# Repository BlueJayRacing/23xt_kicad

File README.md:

# 23xt_kicad, JHU Blue Jay Racing Repository
This is the KiCad Repository for the JHU 23XT DAQ Sub-team.

## Installation and User Guide
GitHub & KiCad Guide: https://docs.google.com/document/d/1nFm-e38JEY4i58-0UFxqdLA5TKqWCrV3EDKR8jGpRfA/edit?usp=sharing 

As a summary, you should be using **KiCad Version 10.0**. All project will be modular, and you should be storing all your step files, symbols, & footprints within the created folders.

Schematic settings & layout settings are described in the guide, as well as component derating.

## Branch Guide
You should be working on a new branch for each revision of your board. It is only when your board gets ordered on JLC that it should be merged with the main branch.

<ins>Branch naming structure:</ins> [0X]-[boardname]_v[version]

Example:
> 01-main_board_v1

<ins>How-To Create a Branch:</ins>

```
git checkout -b [your_branch] main
git push -u origin [your_branch]
```

## KiCad Project Name

Create your KiCad project on YOUR branch, within your current project folder.

<ins>Project filepath:</ins> [your_folder]/[boardname]_v[X]

Example Path:
> 01-main_board/main_board_v1

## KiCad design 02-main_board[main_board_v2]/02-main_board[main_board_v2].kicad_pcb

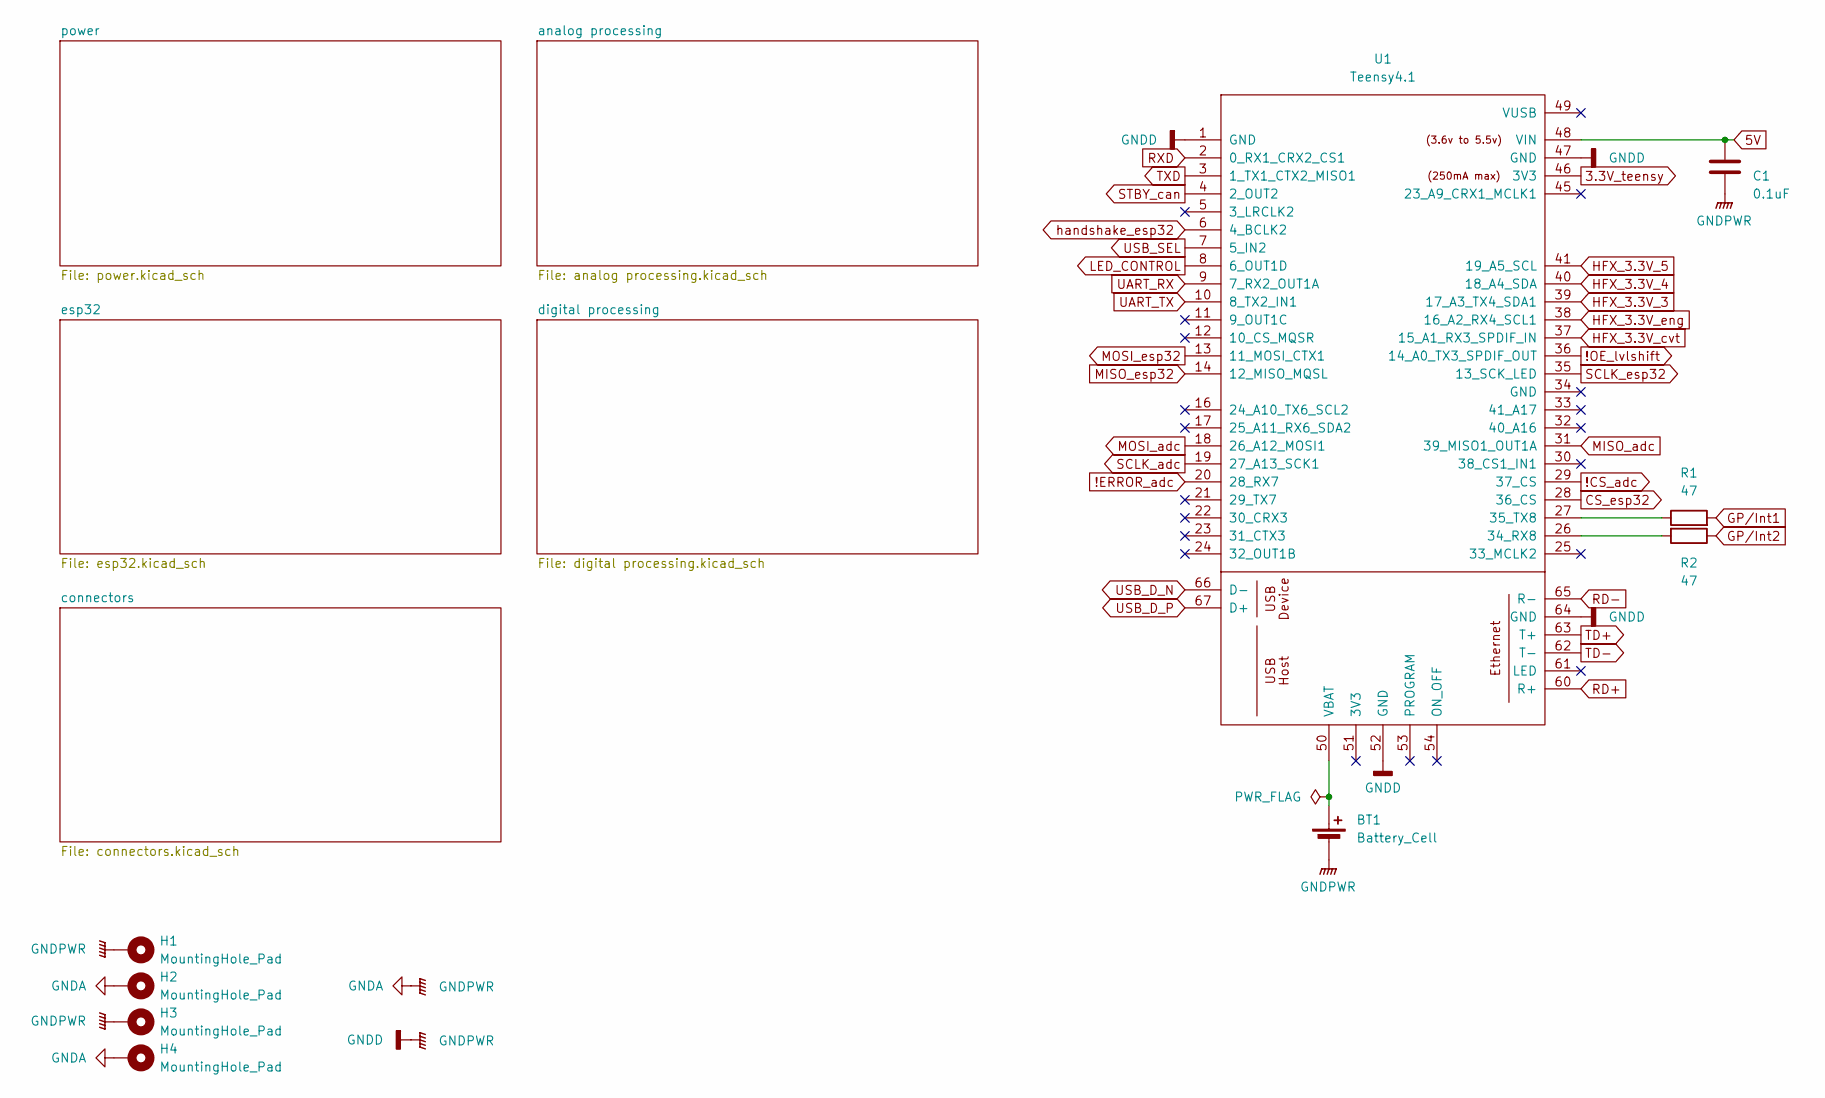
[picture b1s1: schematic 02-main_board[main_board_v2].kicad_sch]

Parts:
BT1: Battery_Cell; BatteryHolder_LINX_BAT-HLD-012-SMT
C1: 0.1uF; C_0603_1608Metric; MPN CC0603KRX7R9BB104; LCSC C14663
H1, H2, H3, H4: MountingHole_Pad; MountingHole_2.5mm_Pad
R1, R2: 47; R_0603_1608Metric; MPN RC0603JR-0747RL; LCSC C23182
U1: Teensy4.1; Teensy41_OG

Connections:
3.3V_teensy: U1.46 (3V3); also elsewhere on the board
5V: C1.2, U1.48 (VIN); also elsewhere on the board
!CS_adc: U1.29 (37_CS); also elsewhere on the board
!ERROR_adc: U1.20 (28_RX7); also elsewhere on the board
!OE_lvlshift: U1.36 (14_A0_TX3_SPDIF_OUT); also elsewhere on the board
CS_esp32: U1.28 (36_CS); also elsewhere on the board
GNDA: BT1.2 (-), C1.1, H1.1 (1_1), H2.1 (1_1), H3.1 (1_1), H4.1 (1_1), U1.1 (GND), U1.47 (GND), U1.52 (GND), U1.64 (GND); also elsewhere on the board
GP/Int1: R1.2; also elsewhere on the board
GP/Int2: R2.1; also elsewhere on the board
HFX_3.3V_3: U1.39 (17_A3_TX4_SDA1); also elsewhere on the board
HFX_3.3V_4: U1.40 (18_A4_SDA); also elsewhere on the board
HFX_3.3V_5: U1.41 (19_A5_SCL); also elsewhere on the board
HFX_3.3V_cvt: U1.37 (15_A1_RX3_SPDIF_IN); also elsewhere on the board
HFX_3.3V_eng: U1.38 (16_A2_RX4_SCL1); also elsewhere on the board
LED_CONTROL: U1.8 (6_OUT1D); also elsewhere on the board
MISO_adc: U1.31 (39_MISO1_OUT1A); also elsewhere on the board
MISO_esp32: U1.14 (12_MISO_MQSL); also elsewhere on the board
MOSI_adc: U1.18 (26_A12_MOSI1); also elsewhere on the board
MOSI_esp32: U1.13 (11_MOSI_CTX1); also elsewhere on the board
unnamed: BT1.1 (+), U1.50 (VBAT)
unnamed: R2.2, U1.26 (34_RX8)
unnamed: R1.1, U1.27 (35_TX8)
RD+: U1.60 (R+); also elsewhere on the board
RD-: U1.65 (R-); also elsewhere on the board
RXD: U1.2 (0_RX1_CRX2_CS1); also elsewhere on the board
SCLK_adc: U1.19 (27_A13_SCK1); also elsewhere on the board
SCLK_esp32: U1.35 (13_SCK_LED); also elsewhere on the board
STBY_can: U1.4 (2_OUT2); also elsewhere on the board
TD+: U1.63 (T+); also elsewhere on the board
TD-: U1.62 (T-); also elsewhere on the board
TXD: U1.3 (1_TX1_CTX2_MISO1); also elsewhere on the board
UART_RX: U1.9 (7_RX2_OUT1A); also elsewhere on the board
UART_TX: U1.10 (8_TX2_IN1); also elsewhere on the board
USB_D_N: U1.66 (D-); also elsewhere on the board
USB_D_P: U1.67 (D+); also elsewhere on the board
USB_SEL: U1.7 (5_IN2); also elsewhere on the board
handshake_esp32: U1.6 (4_BCLK2); also elsewhere on the board

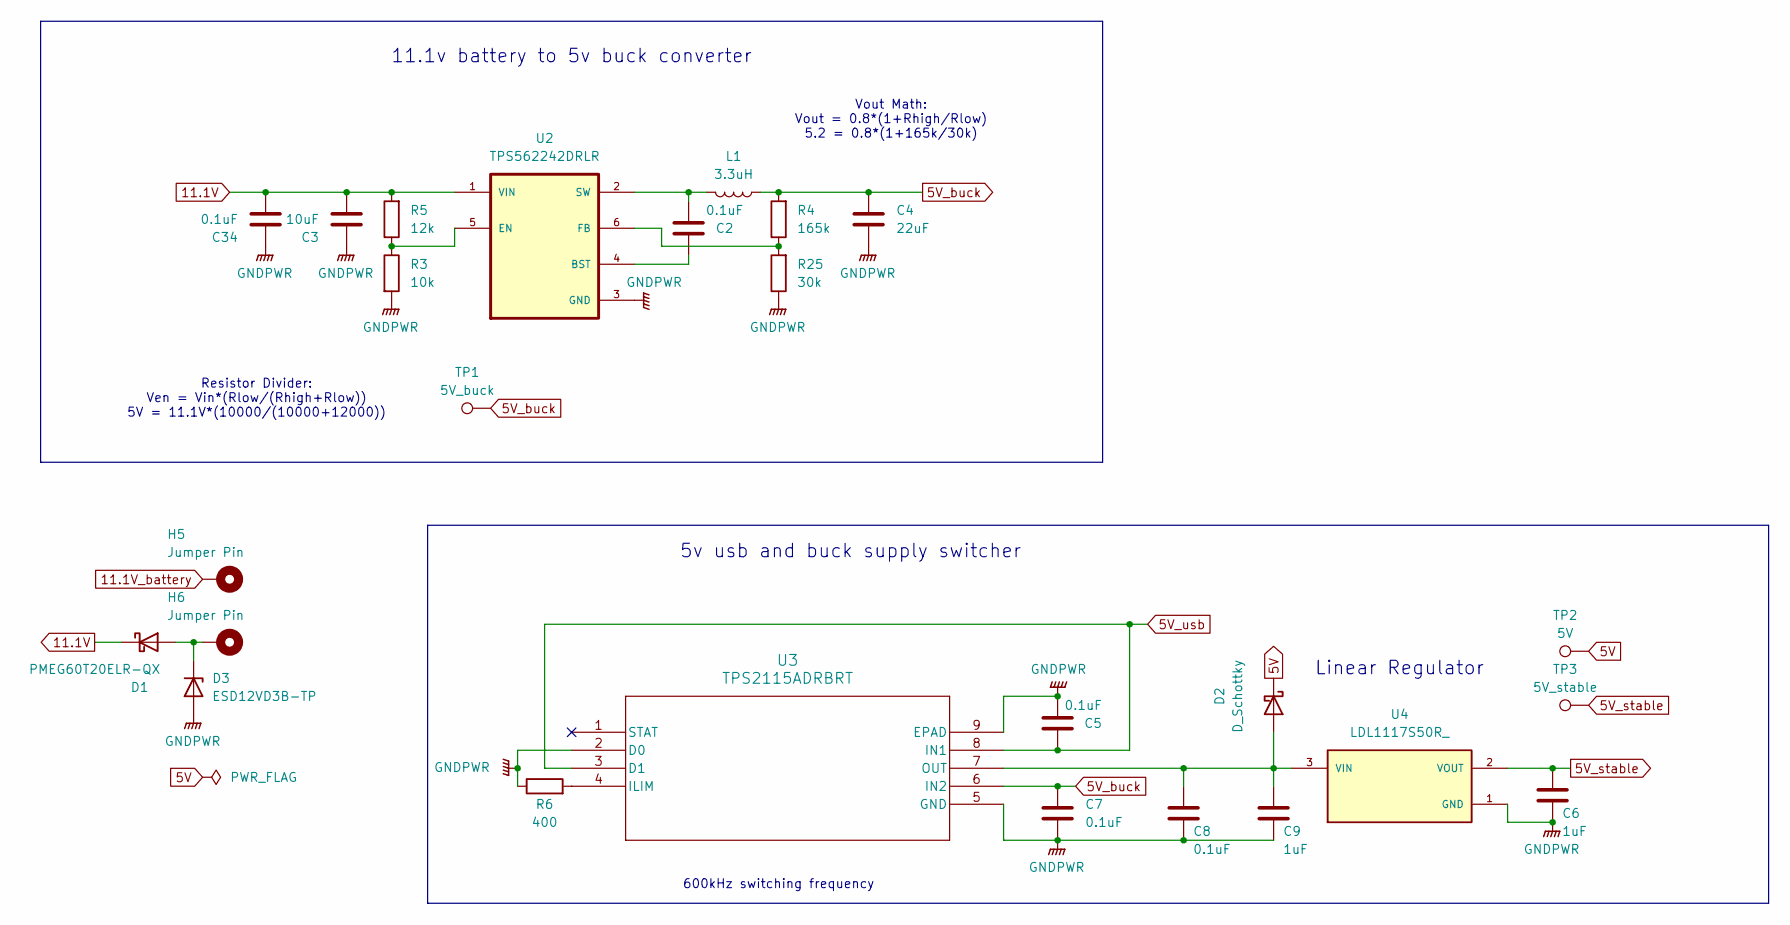
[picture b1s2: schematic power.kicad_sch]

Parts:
C2: 0.1uF; C_0603_1608Metric; MPN CL10B474KO8NNND; LCSC C14663
C3: 10uF; C_0603_1608Metric; MPN GMC10X5R106M16NT; LCSC C96446
C4: 22uF; C_0603_1608Metric; MPN GRM188R61A226ME15D; LCSC C59461
C5, C7, C8: 0.1uF; C_0603_1608Metric; MPN CC0603KRX7R9BB104; LCSC C14663
C6, C9: 1uF; C_0603_1608Metric; MPN CL10A105KA8NFNC; LCSC C15849
C34: 0.1uF; C_0603_1608Metric; MPN CL10A475KO8NNNC; LCSC C14663
D1: PMEG60T20ELR-QX; Nexperia_CFP3_SOD-123W
D2: D_Schottky; Nexperia_CFP3_SOD-123W
D3: ESD12VD3B-TP; D_SOD-323
H5, H6: Jumper Pin; PinHeader_1x01_P2.54mm_Vertical
L1: 3.3uH; IND_TAIYO_NRS4018_TAY; MPN NRS4018T3R3MDGJ
R3: 10k; R_0603_1608Metric; MPN CRCW060310K0FKEA; LCSC C25804
R4: 165k; R_0603_1608Metric; MPN RNCF0603DTE165K
R5: 12k; R_0603_1608Metric; MPN CRCW060312K0FKEA; LCSC C22790
R6: 400; R_0603_1608Metric; MPN RK73H1JTTD4020F
R25: 30k; R_0603_1608Metric; MPN TFAS0603R3002F-T5
TP1: 5V_buck; TestPoint_Pad_1.0x1.0mm
TP2: 5V; TestPoint_Pad_1.0x1.0mm
TP3: 5V_stable; TestPoint_Pad_1.0x1.0mm
U2: TPS562242DRLR; SOT50P160X60-6N; PARTREV A
U3: TPS2115ADRBRT; SON65P300X300X100-9N-D; MPN TPS2115ADRBR
U4: LDL1117S50R_; PARTREV 7

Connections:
5V: D2.1 (K), TP2.1 (1_1); also elsewhere on the board
5V_buck: C4.1, C7.1, L1.1, R4.2, TP1.1 (1_1), U3.6 (IN2)
5V_stable: C6.1, TP3.1 (1_1), U4.2 (VOUT), U4.4 (VOUT); also elsewhere on the board
5V_usb: C5.1, U3.3 (D1), U3.8 (IN1); also elsewhere on the board
11.1V: C3.2, C34.2, D1.1 (K), R5.2, U2.1 (VIN); also elsewhere on the board
11.1V_battery: H5.1 (1_1); also elsewhere on the board
GNDA: C3.1, C4.2, C5.2, C6.2, C7.2, C8.2, C9.2, C34.1, D3.2 (A), R3.2, R6.1, R25.1, U2.3 (GND), U3.2 (D0), U3.5 (GND), U3.9 (EPAD), U4.1 (GND); also elsewhere on the board
unnamed: D1.2 (A), D3.1 (K), H6.1 (1_1)
unnamed: C8.1, C9.1, D2.2 (A), U3.7 (OUT), U4.3 (VIN)
unnamed: C2.1, U2.4 (BST)
unnamed: R3.1, R5.1, U2.5 (EN)
unnamed: R4.1, R25.2, U2.6 (FB)
unnamed: C2.2, L1.2, U2.2 (SW)
unnamed: R6.2, U3.4 (ILIM)

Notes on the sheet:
Resistor Divider: Ven = Vin*(Rlow/(Rhigh+Rlow)) 5V = 11.1V*(10000/(10000+12000))
Vout Math: Vout = 0.8*(1+Rhigh/Rlow) 5.2 = 0.8*(1+165k/30k)
5v usb and buck supply switcher
Linear Regulator
600kHz switching frequency
11.1v battery to 5v buck converter

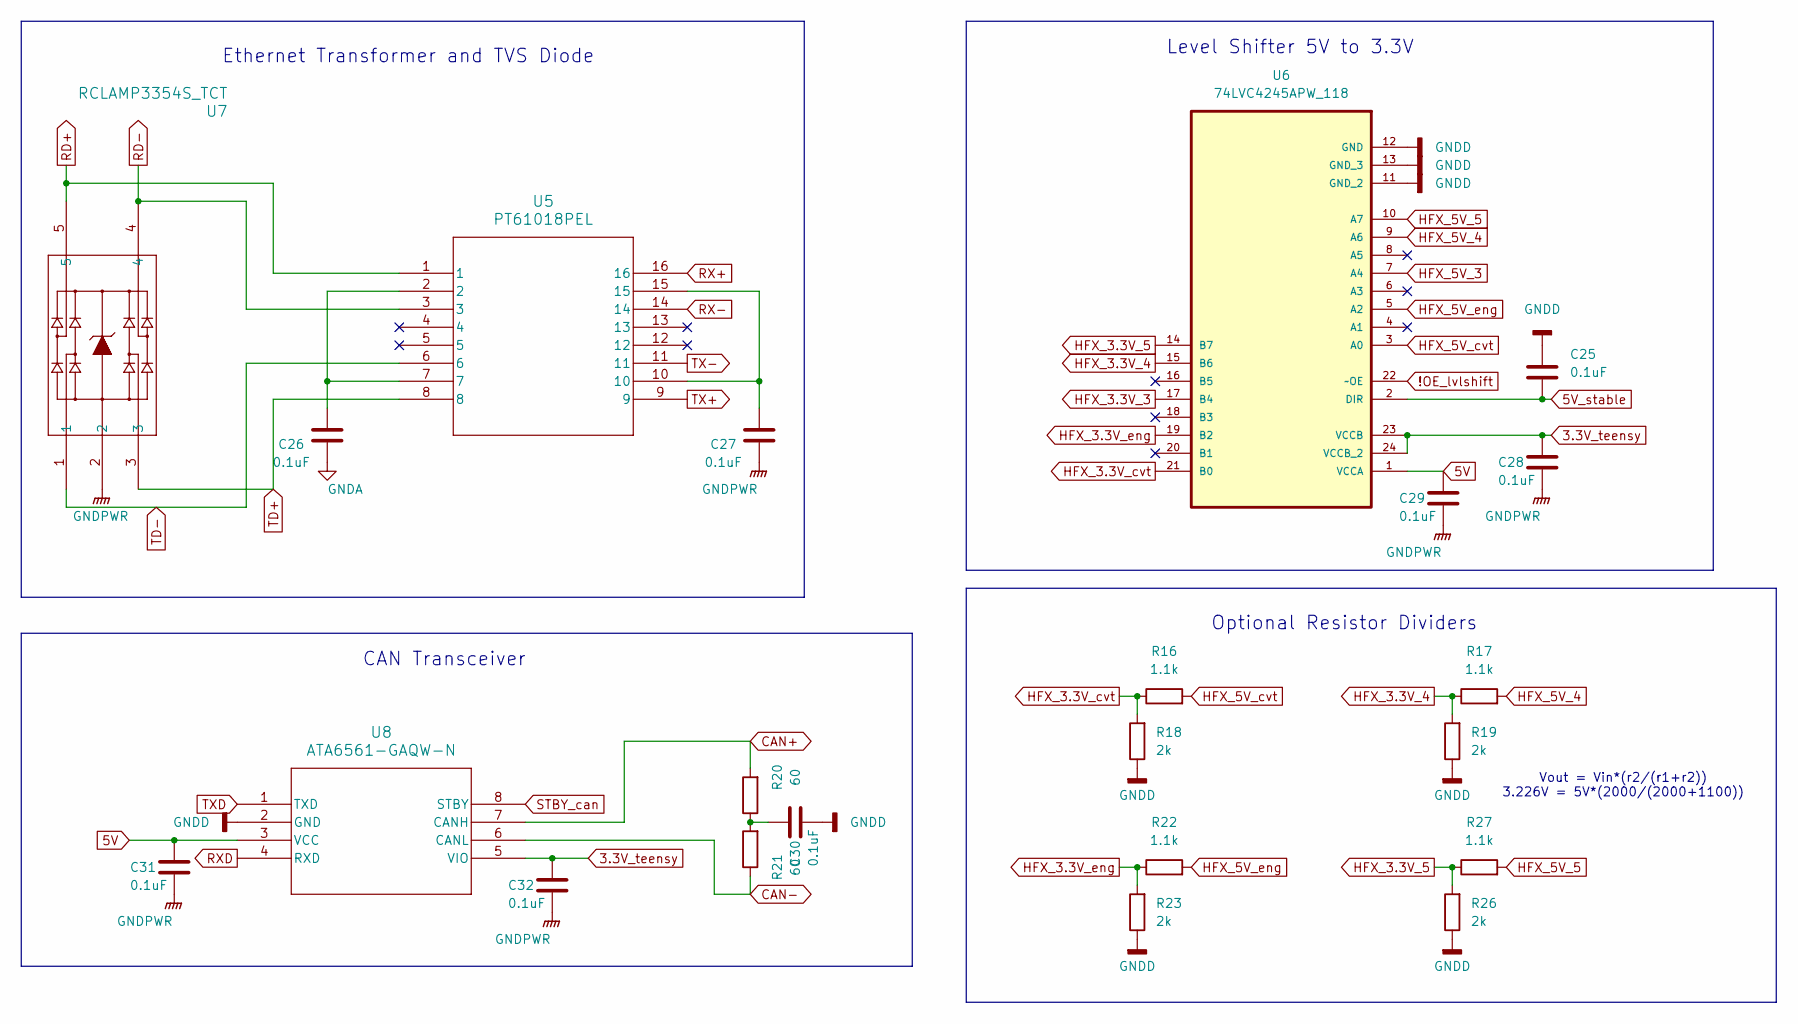
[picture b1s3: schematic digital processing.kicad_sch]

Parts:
C25, C26, C27, C28, C29, C30, C31, C32: 0.1uF; C_0603_1608Metric; MPN CC0603KRX7R9BB104; LCSC C14663
R16, R17, R22, R27: 1.1k; R_0603_1608Metric; MPN RT0603BRD071K1L
R18, R19, R23, R26: 2k; R_0603_1608Metric; MPN RC0603FR-072KL
R20, R21: 60; R_0603_1608Metric; MPN CRCW060360R4FKEA
U5: PT61018PEL; SOIC_PT61018PEL
U6: 74LVC4245APW_118
U7: RCLAMP3354S_TCT
U8: ATA6561-GAQW-N

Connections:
3.3V_teensy: C28.2, C32.2, U6.23 (VCCB), U6.24 (VCCB_2), U8.5 (VIO); also elsewhere on the board
5V: C29.2, C31.2, U6.1 (VCCA), U8.3 (VCC); also elsewhere on the board
5V_stable: C25.1, U6.2 (DIR); also elsewhere on the board
!OE_lvlshift: U6.22 (~OE); also elsewhere on the board
CAN+: R20.2, U8.7 (CANH); also elsewhere on the board
CAN-: R21.1, U8.6 (CANL); also elsewhere on the board
GNDA: C25.2, C26.2, C27.2, C28.1, C29.1, C30.1, C31.1, C32.1, R18.1, R19.1, R23.1, R26.1, U6.11 (GND_2), U6.12 (GND), U6.13 (GND_3), U7.2, U8.2 (GND); also elsewhere on the board
HFX_3.3V_3: U6.17 (B4); also elsewhere on the board
HFX_3.3V_4: R17.1, R19.2, U6.15 (B6); also elsewhere on the board
HFX_3.3V_5: R26.2, R27.1, U6.14 (B7); also elsewhere on the board
HFX_3.3V_cvt: R16.1, R18.2, U6.21 (B0); also elsewhere on the board
HFX_3.3V_eng: R22.1, R23.2, U6.19 (B2); also elsewhere on the board
HFX_5V_3: U6.7 (A4); also elsewhere on the board
HFX_5V_4: R17.2, U6.9 (A6); also elsewhere on the board
HFX_5V_5: R27.2, U6.10 (A7); also elsewhere on the board
HFX_5V_cvt: R16.2, U6.3 (A0); also elsewhere on the board
HFX_5V_eng: R22.2, U6.5 (A2); also elsewhere on the board
unnamed: C26.1, U5.2, U5.7
unnamed: C27.1, U5.10, U5.15
unnamed: C30.2, R20.1, R21.2
RD+: U5.1, U7.5; also elsewhere on the board
RD-: U5.3, U7.4; also elsewhere on the board
RX+: U5.16; also elsewhere on the board
RX-: U5.14; also elsewhere on the board
RXD: U8.4 (RXD); also elsewhere on the board
STBY_can: U8.8 (STBY); also elsewhere on the board
TD+: U5.8, U7.3; also elsewhere on the board
TD-: U5.6, U7.1; also elsewhere on the board
TX+: U5.9; also elsewhere on the board
TX-: U5.11; also elsewhere on the board
TXD: U8.1 (TXD); also elsewhere on the board

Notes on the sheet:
Optional Resistor Dividers
Vout = Vin*(r2/(r1+r2)) 3.226V = 5V*(2000/(2000+1100))
Level Shifter 5V to 3.3V
Ethernet Transformer and TVS Diode
CAN Transceiver

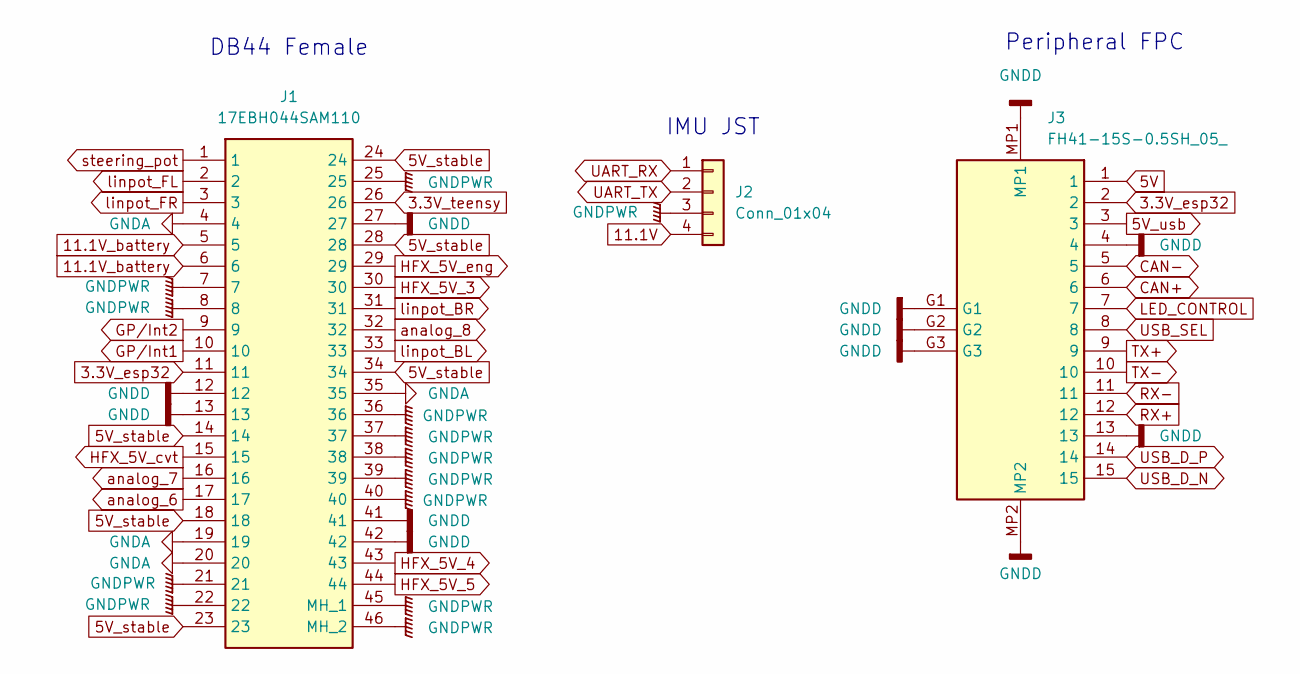
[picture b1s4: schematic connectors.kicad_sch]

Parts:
J1: 17EBH044SAM110; Manufacturer_Part_Number 17EBH044SAM110
J2: Conn_01x04; JST_EH_B4B-EH-A_1x04_P2.50mm_Vertical
J3: FH41-15S-0.5SH_05_; FH4115S05SH05; Mouser Part Number 798-FH4115S05SH05

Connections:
3.3V_esp32: J1.11, J3.2; also elsewhere on the board
3.3V_teensy: J1.26; also elsewhere on the board
5V: J3.1; also elsewhere on the board
5V_stable: J1.14, J1.18, J1.23, J1.24, J1.28, J1.34; also elsewhere on the board
5V_usb: J3.3; also elsewhere on the board
11.1V: J2.4; also elsewhere on the board
11.1V_battery: J1.5, J1.6; also elsewhere on the board
CAN+: J3.6; also elsewhere on the board
CAN-: J3.5; also elsewhere on the board
GNDA: J1.4, J1.7, J1.8, J1.12, J1.13, J1.19, J1.20, J1.21, J1.22, J1.25, J1.27, J1.35, J1.36, J1.37, J1.38, J1.39, J1.40, J1.41, J1.42, J1.45 (MH_1), J1.46 (MH_2), J2.3, J3.4, J3.13, J3.G1, J3.G2, J3.G3, J3.MP1, J3.MP2; also elsewhere on the board
GP/Int1: J1.10; also elsewhere on the board
GP/Int2: J1.9; also elsewhere on the board
HFX_5V_3: J1.30; also elsewhere on the board
HFX_5V_4: J1.43; also elsewhere on the board
HFX_5V_5: J1.44; also elsewhere on the board
HFX_5V_cvt: J1.15; also elsewhere on the board
HFX_5V_eng: J1.29; also elsewhere on the board
LED_CONTROL: J3.7; also elsewhere on the board
RX+: J3.12; also elsewhere on the board
RX-: J3.11; also elsewhere on the board
TX+: J3.9; also elsewhere on the board
TX-: J3.10; also elsewhere on the board
UART_RX: J2.1; also elsewhere on the board
UART_TX: J2.2; also elsewhere on the board
USB_D_N: J3.15; also elsewhere on the board
USB_D_P: J3.14; also elsewhere on the board
USB_SEL: J3.8; also elsewhere on the board
analog_6: J1.17; also elsewhere on the board
analog_7: J1.16; also elsewhere on the board
analog_8: J1.32; also elsewhere on the board
linpot_BL: J1.33; also elsewhere on the board
linpot_BR: J1.31; also elsewhere on the board
linpot_FL: J1.2; also elsewhere on the board
linpot_FR: J1.3; also elsewhere on the board
steering_pot: J1.1; also elsewhere on the board

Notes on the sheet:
DB44 Female
Peripheral FPC
IMU JST

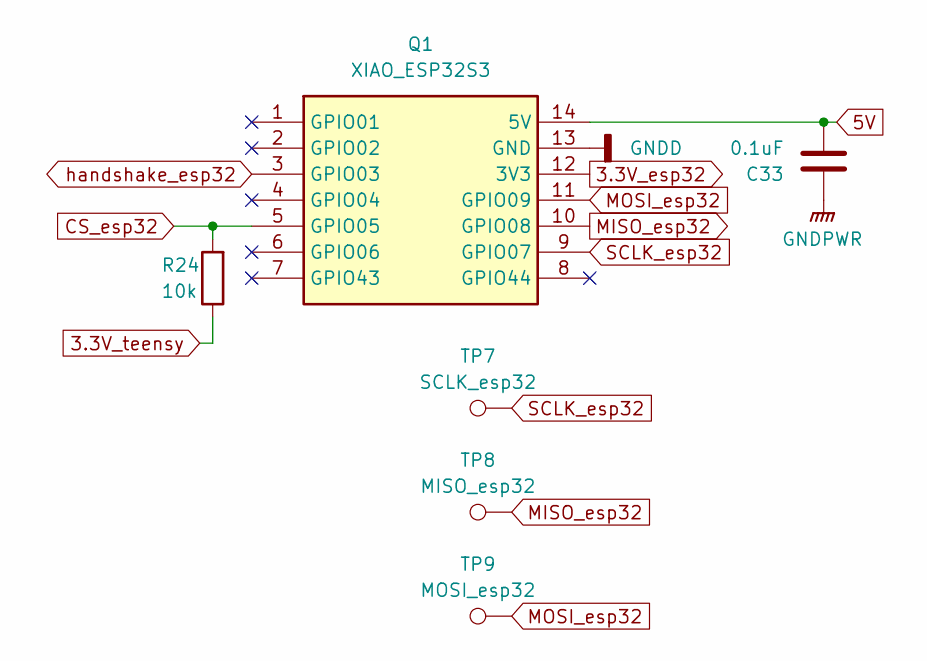
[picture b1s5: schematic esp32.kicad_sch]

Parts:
C33: 0.1uF; C_0603_1608Metric; MPN CC0603KRX7R9BB104; LCSC C14663
Q1: XIAO_ESP32S3; Manufacturer_Part_Number XIAO ESP32S3
R24: 10k; R_0603_1608Metric; MPN CRCW060310K0FKEA; LCSC C25804
TP7: SCLK_esp32; TestPoint_Pad_1.0x1.0mm
TP8: MISO_esp32; TestPoint_Pad_1.0x1.0mm
TP9: MOSI_esp32; TestPoint_Pad_1.0x1.0mm

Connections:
3.3V_esp32: Q1.12 (3V3); also elsewhere on the board
3.3V_teensy: R24.1; also elsewhere on the board
5V: C33.2, Q1.14 (5V); also elsewhere on the board
CS_esp32: Q1.5 (GPIO05), R24.2; also elsewhere on the board
GNDA: C33.1, Q1.13 (GND); also elsewhere on the board
MISO_esp32: Q1.10 (GPIO08), TP8.1 (1_1); also elsewhere on the board
MOSI_esp32: Q1.11 (GPIO09), TP9.1 (1_1); also elsewhere on the board
SCLK_esp32: Q1.9 (GPIO07), TP7.1 (1_1); also elsewhere on the board
handshake_esp32: Q1.3 (GPIO03); also elsewhere on the board

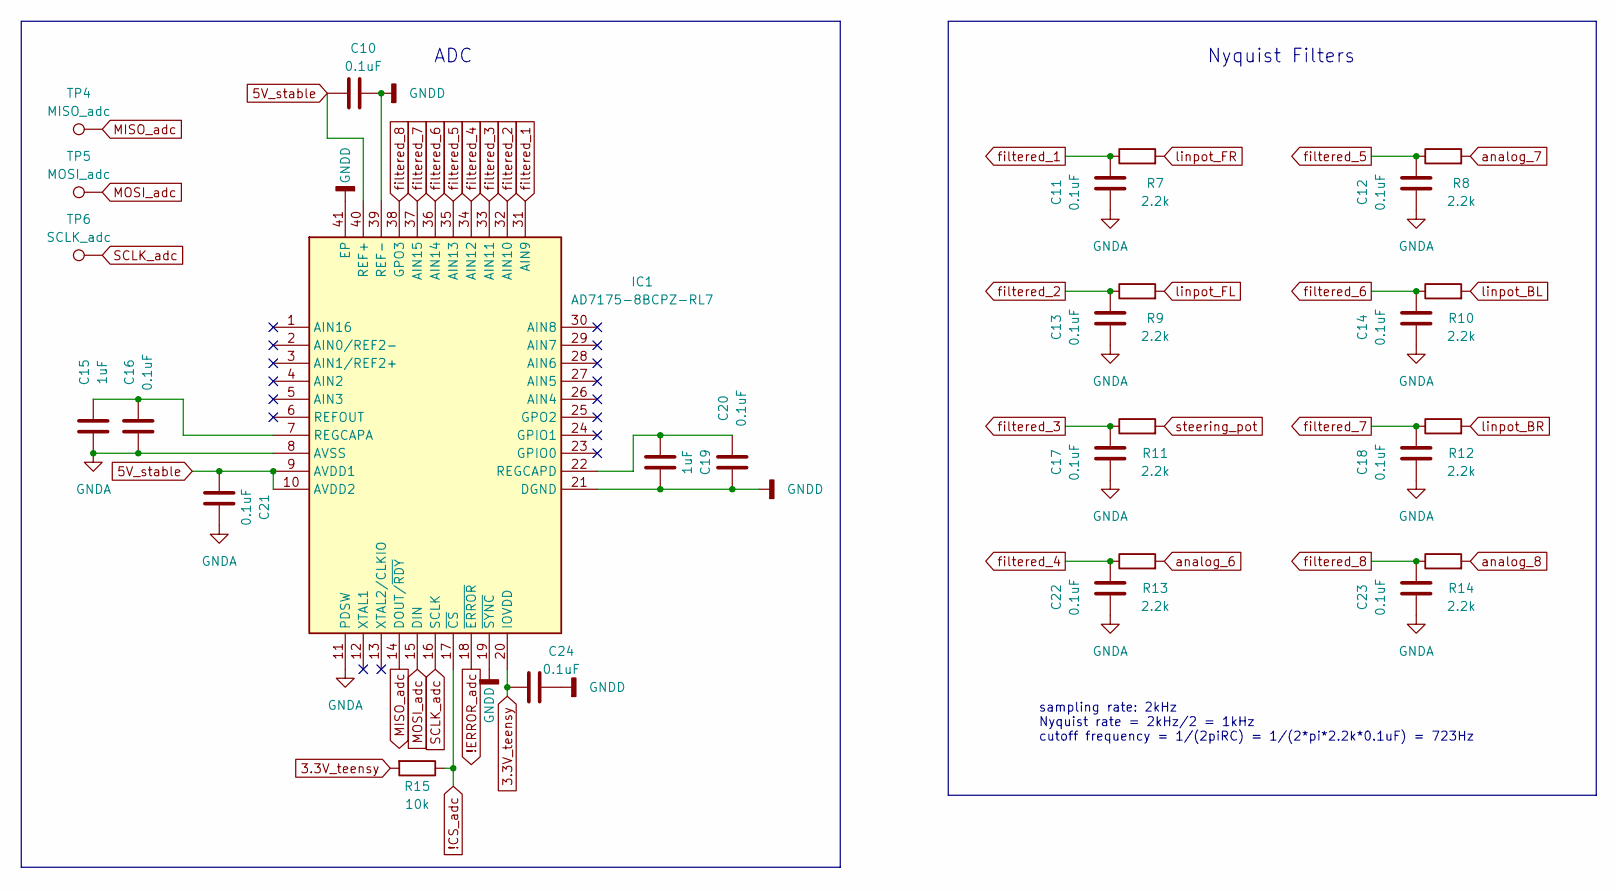
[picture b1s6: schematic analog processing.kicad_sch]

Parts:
C10, C11, C12, C13, C14, C16, C17, C18, C20, C21, C22, C23, C24: 0.1uF; C_0603_1608Metric; MPN CC0603KRX7R9BB104; LCSC C14663
C15, C19: 1uF; C_0603_1608Metric; MPN CL10A105KA8NFNC; LCSC C15849
IC1: AD7175-8BCPZ-RL7; Manufacturer_Part_Number AD7175-8BCPZ-RL7; Mouser Part Number 584-AD7175-8BCPZ-RL7
R7, R8, R9, R10, R11, R12, R13, R14: 2.2k; R_0603_1608Metric; MPN RC0603FR-072K2L; LCSC C4190
R15: 10k; R_0603_1608Metric; MPN CRCW060310K0FKEA; LCSC C25804
TP4: MISO_adc; TestPoint_Pad_1.0x1.0mm
TP5: MOSI_adc; TestPoint_Pad_1.0x1.0mm
TP6: SCLK_adc; TestPoint_Pad_1.0x1.0mm

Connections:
3.3V_teensy: C24.1, IC1.20 (IOVDD), R15.2; also elsewhere on the board
5V_stable: C10.1, C21.1, IC1.9 (AVDD1), IC1.10 (AVDD2), IC1.40 (REF+); also elsewhere on the board
!CS_adc: IC1.17 (~CS), R15.1; also elsewhere on the board
!ERROR_adc: IC1.18 (~ERROR); also elsewhere on the board
GNDA: C10.2, C11.1, C12.1, C13.1, C14.1, C15.1, C16.1, C17.1, C18.1, C19.2, C20.1, C21.2, C22.1, C23.1, C24.2, IC1.8 (AVSS), IC1.11 (PDSW), IC1.19 (~SYNC), IC1.21 (DGND), IC1.39 (REF-), IC1.41 (EP); also elsewhere on the board
MISO_adc: IC1.14 (DOUT/~RDY), TP4.1 (1_1); also elsewhere on the board
MOSI_adc: IC1.15 (DIN), TP5.1 (1_1); also elsewhere on the board
unnamed: C15.2, C16.2, IC1.7 (REGCAPA)
unnamed: C19.1, C20.2, IC1.22 (REGCAPD)
SCLK_adc: IC1.16 (SCLK), TP6.1 (1_1); also elsewhere on the board
analog_6: R13.2; also elsewhere on the board
analog_7: R8.2; also elsewhere on the board
analog_8: R14.2; also elsewhere on the board
filtered_1: C11.2, IC1.31 (AIN9), R7.1
filtered_2: C13.2, IC1.32 (AIN10), R9.1
filtered_3: C17.2, IC1.33 (AIN11), R11.1
filtered_4: C22.2, IC1.34 (AIN12), R13.1
filtered_5: C12.2, IC1.35 (AIN13), R8.1
filtered_6: C14.2, IC1.36 (AIN14), R10.1
filtered_7: C18.2, IC1.37 (AIN15), R12.1
filtered_8: C23.2, IC1.38 (GPO3), R14.1
linpot_BL: R10.2; also elsewhere on the board
linpot_BR: R12.2; also elsewhere on the board
linpot_FL: R9.2; also elsewhere on the board
linpot_FR: R7.2; also elsewhere on the board
steering_pot: R11.2; also elsewhere on the board

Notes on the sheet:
Nyquist Filters
sampling rate: 2kHz Nyquist rate = 2kHz/2 = 1kHz cutoff frequency = 1/(2piRC) = 1/(2*pi*2.2k*0.1uF) = 723Hz
ADC

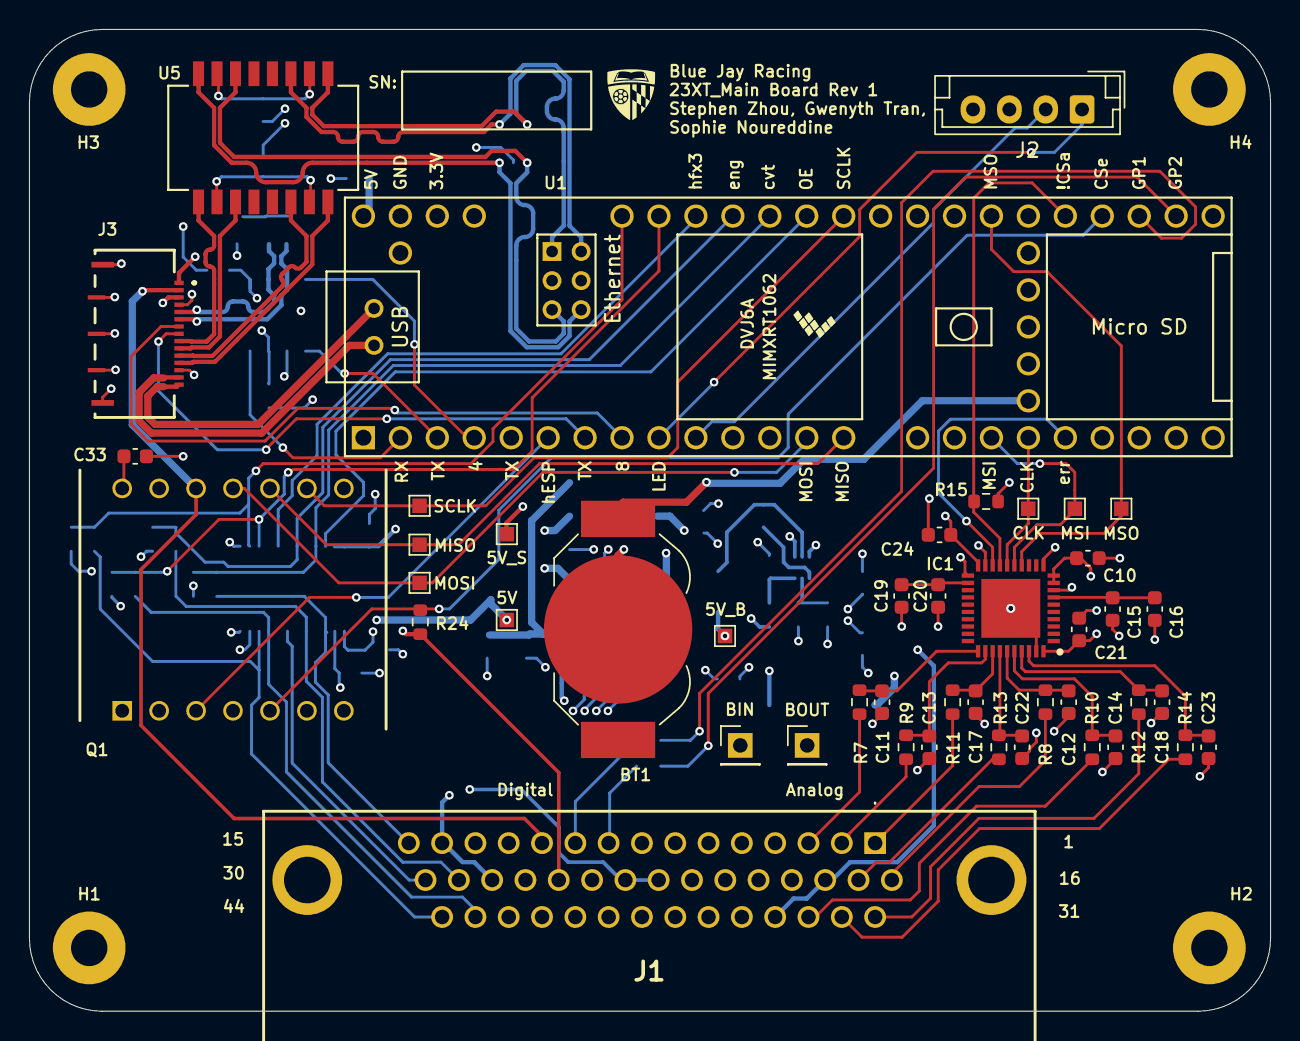
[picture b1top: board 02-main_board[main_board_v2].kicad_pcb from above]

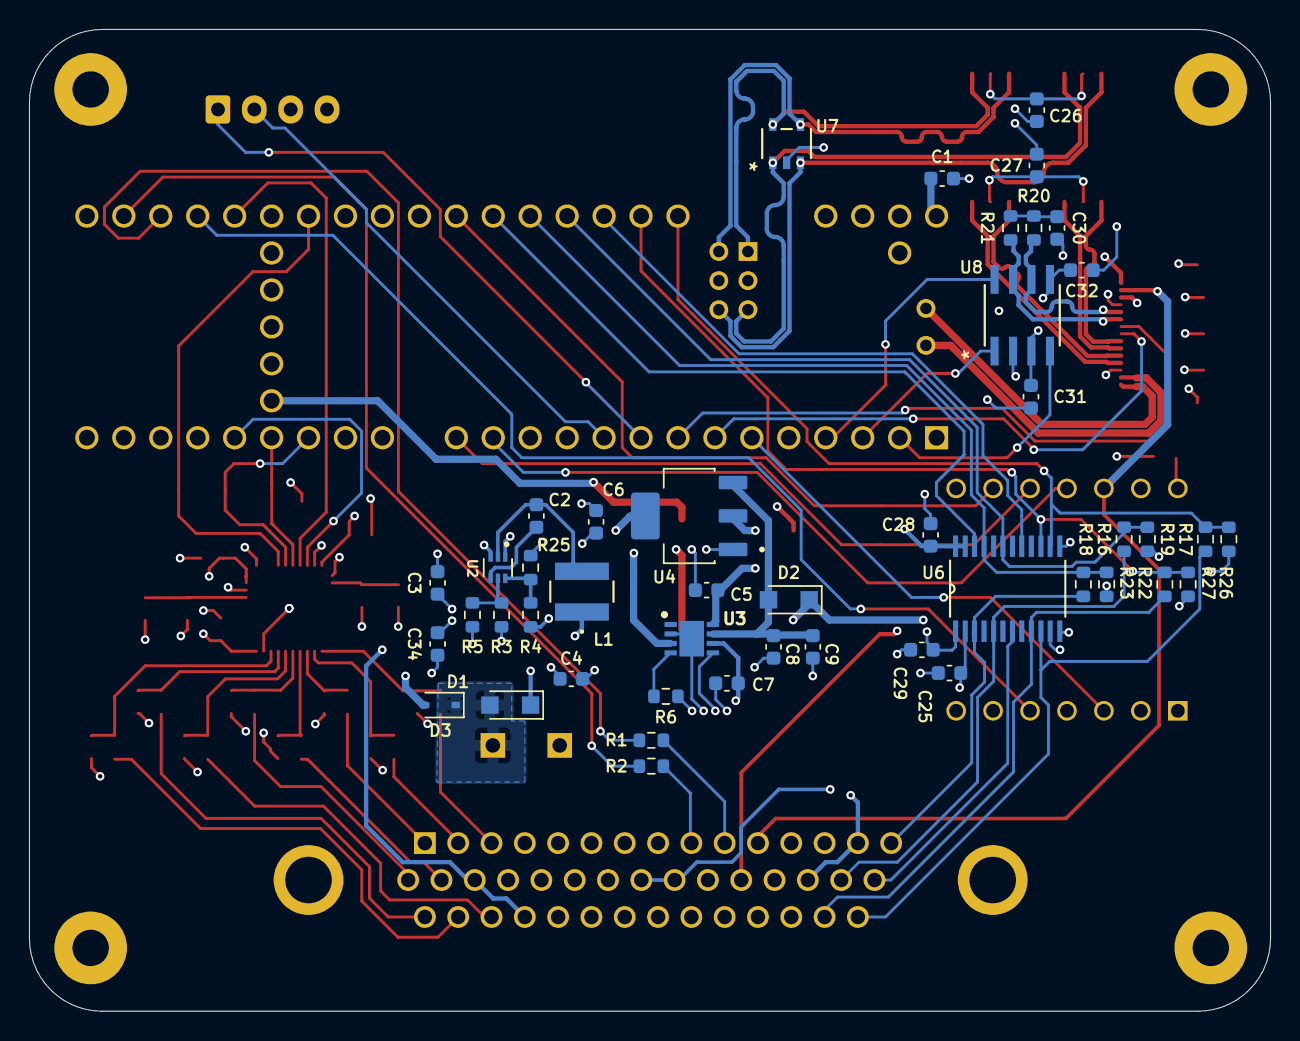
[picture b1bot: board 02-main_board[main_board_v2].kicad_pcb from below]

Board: 4 copper layers, 85.3 x 67.5 mm, 94 parts (45 on the bottom side), 82 nets.

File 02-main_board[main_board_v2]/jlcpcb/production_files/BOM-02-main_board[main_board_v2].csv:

Comment,Designator,Footprint,LCSC,Quantity
0.1uF,"C1,C10,C11,C12,C13,C14,C16,C17,C18,C2,C20,C21,C22,C23,C24,C25,C26,C27,C28,C29,C30,C31,C32,C33,C34,C5,C7,C8",C_0603_1608Metric,C14663,28
10k,"R15,R24,R3",R_0603_1608Metric,C25804,3
10uF,C3,C_0603_1608Metric,C96446,1
12k,R5,R_0603_1608Metric,C22790,1
1uF,"C15,C19,C6,C9",C_0603_1608Metric,C15849,4
2.2k,"R10,R11,R12,R13,R14,R7,R8,R9",R_0603_1608Metric,C4190,8
22uF,C4,C_0603_1608Metric,C59461,1
3.3uH,L1,IND_TAIYO_NRS4018_TAY,C92960,1
400,R6,R_0603_1608Metric,C5841024,1
47,"R1,R2",R_0603_1608Metric,C23182,2
74LVC4245APW_118,U6,74LVC4245APW_118,C6091,1
AD7175-8BCPZ-RL7,IC1,AD7175-8BCPZ-RL7,C578395,1
ATA6561-GAQW-N,U8,ATA6561-GAQW-N,C616016,1
ESD12VD3B-TP,D3,D_SOD-323,C435886,1
LDL1117S50R_,U4,LDL1117S50R_,C970558,1
PMEG60T20ELR-QX,D1,Nexperia_CFP3_SOD-123W,C6629174,1
PT61018PEL,U5,SOIC_PT61018PEL,C840586,1
RCLAMP3354S_TCT,U7,RCLAMP3354S_TCT,C441850,1
TPS2115ADRBRT,U3,SON65P300X300X100-9N-D,C140321,1
TPS562242DRLR,U2,SOT50P160X60-6N,C19272253,1
345k,R4,R_0603_1608Metric,,1
